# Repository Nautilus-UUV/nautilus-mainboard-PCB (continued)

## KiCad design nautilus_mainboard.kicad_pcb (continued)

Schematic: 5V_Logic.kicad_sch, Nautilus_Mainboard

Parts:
C35, C36: 10uF; C_1210_3225Metric; Voltage 100V; Tolerance 10%; MPN GRM32EC72A106KE05; LCSC C5444485
C37, C38, C40: 100nF; C_0603_1608Metric; Voltage 50V; Tolerance 10%; MPN 885012206095; LCSC CXXXXX
C41: 330nF; C_0603_1608Metric; Voltage 10V; Tolerance 20%; MPN 885012106007; LCSC CXXXXX
C53: 47uF; C_0805_2012Metric; Voltage 10V; Tolerance 20%; MPN GRM21BR61A476ME15; LCSC C124129
IC5: TPS2121RUXT; TI_Switchover_TPS2121RUXT; Mouser Part Number 595-TPS2121RUXT
R22: 22k; R_0603_1608Metric; Tolerance 1 %; MPN 560112116022; LCSC CXXXXX

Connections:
+5V: C40.1, C53.1, IC5.1 (OUT_1), IC5.8 (OUT_2); also elsewhere on the board
/Power_logic/5V_Logic/Battery_Out_5V: C35.1, C37.1, IC5.6 (PR1), IC5.7 (IN1); also elsewhere on the board
/Power_logic/5V_Logic/USB_Out_5V: C36.1, C38.1, IC5.2 (IN2); also elsewhere on the board
GND: C35.2, C36.2, C37.2, C38.2, C40.2, C41.1, C53.2, IC5.3 (CP2), IC5.4 (OV2), IC5.5 (OV1), IC5.12 (GND), R22.1; also elsewhere on the board
unnamed: IC5.10 (ILIM), R22.2
unnamed: C41.2, IC5.11 (SS)

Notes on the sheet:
for questions about wiring etc please consult the datasheet...
if the USB-only cold start "disconnects" we can try to bump SS to 470nF instead of 330nF.
100nF CLOSE
https://www.ti.com/lit/ds/symlink/tps2120.pdf?ts=1761678178328
PR1 > CP2 -> IN1 has prio

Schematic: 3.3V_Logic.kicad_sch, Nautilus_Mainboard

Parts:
C21, C22: 10uF; C_1210_3225Metric; Voltage 100V; Tolerance 10%; MPN GRM32EC72A106KE05; LCSC C5444485
C23, C24, C26: 100nF; C_0603_1608Metric; Voltage 50V; Tolerance 10%; MPN 885012206095; LCSC CXXXXX
C25: 330nF; C_0603_1608Metric; Voltage 10V; Tolerance 20%; MPN 885012106007; LCSC CXXXXX
C27: 47uF; C_0805_2012Metric; Voltage 10V; Tolerance 20%; MPN GRM21BR61A476ME15; LCSC C124129
IC6: TPS2121RUXT; TI_Switchover_TPS2121RUXT; Mouser Part Number 595-TPS2121RUXT
R17: 68k; R_0603_1608Metric; Tolerance 1 %; MPN 560112116064; LCSC CXXXXX

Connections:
+3.3V: C26.1, C27.1, IC6.1 (OUT_1), IC6.8 (OUT_2); also elsewhere on the board
/Power_logic/3.3V_Logic/Battery_Out_3.3V: C21.1, C23.1, IC6.6 (PR1), IC6.7 (IN1); also elsewhere on the board
/Power_logic/3.3V_Logic/STM_Plug_3.3V: C22.1, C24.1, IC6.2 (IN2); also elsewhere on the board
GND: C21.2, C22.2, C23.2, C24.2, C25.1, C26.2, C27.2, IC6.3 (CP2), IC6.4 (OV2), IC6.5 (OV1), IC6.12 (GND), R17.2; also elsewhere on the board
unnamed: IC6.10 (ILIM), R17.1
unnamed: C25.2, IC6.11 (SS)

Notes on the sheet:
if the USB-only cold start "disconnects" we can try to bump SS to 470nF instead of 330nF.
22 kΩ → ~4.55 A 39 kΩ → ~2.78 A 50 kΩ → ~2.25 A 56 kΩ → ~2.04 A 68 kΩ → ~1.72 A 100 kΩ → ~1.24 A
Pin 10: 68k leads to about 1.72A (should be enough for STM)
[R] = [kOhm] 65.2 / R^0.861
PR1 > CP2 -> IN1 has prio

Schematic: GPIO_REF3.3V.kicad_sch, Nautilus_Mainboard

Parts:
C39, C50, C51, C52: 100nF; C_0603_1608Metric; Voltage 50V; Tolerance 10%; MPN 885012206095; LCSC CXXXXX
C48, C49: 10uF; C_1210_3225Metric; Voltage 100V; Tolerance 10%; MPN GRM32EC72A106KE05; LCSC C5444485
C54: 47uF; C_0805_2012Metric; Voltage 10V; Tolerance 20%; MPN GRM21BR61A476ME15; LCSC C124129
IC3: TPS2121RUXT; TI_Switchover_TPS2121RUXT; Mouser Part Number 595-TPS2121RUXT
R14, R27: 100k; R_0603_1608Metric; Tolerance 1 %; MPN 560112116004; LCSC CXXXXX
TP13: Test Point; TestPoint_Pad_D1.5mm

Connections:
/CM4/GPIO_VREF_3.3V: C52.1, C54.1, IC3.1 (OUT_1), IC3.8 (OUT_2), R14.1, TP13.1; also elsewhere on the board
/Power_logic/GPIO_REF3.3V/CM4_OUT_3.3V: C49.1, C51.1, IC3.2 (IN2); also elsewhere on the board
/Power_logic/GPIO_REF3.3V/STM_IN_3.3V: C48.1, C50.1, IC3.6 (PR1), IC3.7 (IN1); also elsewhere on the board
GND: C39.1, C48.2, C49.2, C50.2, C51.2, C52.2, C54.2, IC3.3 (CP2), IC3.4 (OV2), IC3.5 (OV1), IC3.12 (GND), R14.2, R27.1; also elsewhere on the board
unnamed: IC3.10 (ILIM), R27.2
unnamed: C39.2, IC3.11 (SS)

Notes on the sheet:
Pin SS (11): 100nF soft start cap more than enoug as virtually no load at all at vref
PR1 > CP2 -> IN1 has prio
[R] = [kOhm] 65.2 / R^0.861
100kOhm pulldown so Vref is low if everything is off (not floating)
22 kΩ → ~4.55 A 39 kΩ → ~2.78 A 50 kΩ → ~2.25 A 56 kΩ → ~2.04 A 68 kΩ → ~1.72 A 100 kΩ → ~1.24 A
Pin 10: 100kOhm leads to about 1.24A (absolute overkill)

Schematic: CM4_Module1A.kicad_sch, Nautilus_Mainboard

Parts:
C1, C2, C3, C4, C5, C6: 100nF; C_0603_1608Metric; Voltage 50V; Tolerance 10%; MPN 885012206095; LCSC CXXXXX
C7, C42: 1uF; C_0603_1608Metric; Voltage 50V; Tolerance 10%; MPN 885012206126; LCSC CXXXXX
C47: 10uF; C_1210_3225Metric; Voltage 100V; Tolerance 10%; MPN GRM32EC72A106KE05; LCSC C5444485
Module1: DF40C-100DS-0.4V(51); Con-Raspberry-Pi-4-Compute-Module; Part Description 100 Position Connector Receptacle, Cent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; LCSC N/A
Q2: 50V; onsemi_Mosfet_BSS138; PARTREV 30 Jan 2018

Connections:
+5V: C1.1, C2.1, C3.1, C4.1, C5.1, C6.1, C7.1, C42.1, C47.1, Module1.77 (+5v_(Input)), Module1.79 (+5v_(Input)), Module1.81 (+5v_(Input)), Module1.83 (+5v_(Input)), Module1.85 (+5v_(Input)), Module1.87 (+5v_(Input)); also elsewhere on the board
/CM4/CM4_Module1A/CM4_LED1/nPWR_LED: Module1.95 (nPI_LED_PWR); also elsewhere on the board
/CM4/CM4_Module1A/CM4_LED2/PI_nLED_Activity: Module1.21 (PI_nLED_Activity); also elsewhere on the board
/CM4/CM4_Module1A/ETH_LED_G: Module1.15 (Ethernet_nLED3(3.3v)); also elsewhere on the board
/CM4/CM4_Module1A/ETH_LED_Y: Module1.17 (Ethernet_nLED2(3.3v)); also elsewhere on the board
/CM4/CM4_Module1A/GLOBAL_EN: Module1.99 (Global_EN), Q2.3
/CM4/CM4_Module1A/GPIO2: Module1.58 (GPIO2)
/CM4/CM4_Module1A/GPIO3: Module1.56 (GPIO3)
/CM4/CM4_Module1A/GPIO4: Module1.54 (GPIO4)
/CM4/CM4_Module1A/GPIO5: Module1.34 (GPIO5)
/CM4/CM4_Module1A/GPIO6: Module1.30 (GPIO6)
/CM4/CM4_Module1A/GPIO7: Module1.37 (GPIO7)
/CM4/CM4_Module1A/GPIO8: Module1.39 (GPIO8)
/CM4/CM4_Module1A/GPIO9: Module1.40 (GPIO9)
/CM4/CM4_Module1A/GPIO10: Module1.44 (GPIO10)
/CM4/CM4_Module1A/GPIO11: Module1.38 (GPIO11)
/CM4/CM4_Module1A/GPIO12: Module1.31 (GPIO12)
/CM4/CM4_Module1A/GPIO13: Module1.28 (GPIO13)
/CM4/CM4_Module1A/GPIO16: Module1.29 (GPIO16)
/CM4/CM4_Module1A/GPIO17: Module1.50 (GPIO17)
/CM4/CM4_Module1A/GPIO18: Module1.49 (GPIO18)
/CM4/CM4_Module1A/GPIO19: Module1.26 (GPIO19)
/CM4/CM4_Module1A/GPIO20: Module1.27 (GPIO20)
/CM4/CM4_Module1A/GPIO21: Module1.25 (GPIO21)
/CM4/CM4_Module1A/GPIO22: Module1.46 (GPIO22)
/CM4/CM4_Module1A/GPIO23: Module1.47 (GPIO23)
/CM4/CM4_Module1A/GPIO24: Module1.45 (GPIO24)
/CM4/CM4_Module1A/GPIO25: Module1.41 (GPIO25)
/CM4/CM4_Module1A/GPIO26: Module1.24 (GPIO26)
/CM4/CM4_Module1A/GPIO27: Module1.48 (GPIO27)
/CM4/CM4_Out_3.3V: Module1.84 (+3.3v_(Output)), Module1.86 (+3.3v_(Output)); also elsewhere on the board
/CM4/GLOBAL_EN_CM4: Q2.1; also elsewhere on the board
/CM4/GPIO_VREF_3.3V: Module1.78 (GPIO_VREF(1.8v/3.3v_Input)); also elsewhere on the board
/CM4/RUN_PG: Module1.92 (RUN_PG); also elsewhere on the board
/CM4/TRD0.D+: Module1.12 (Ethernet_Pair0_P); also elsewhere on the board
/CM4/TRD0.D-: Module1.10 (Ethernet_Pair0_N); also elsewhere on the board
/CM4/TRD1.D+: Module1.4 (Ethernet_Pair1_P); also elsewhere on the board
/CM4/TRD1.D-: Module1.6 (Ethernet_Pair1_N); also elsewhere on the board
/CM4/TRD2.D+: Module1.11 (Ethernet_Pair2_P); also elsewhere on the board
/CM4/TRD2.D-: Module1.9 (Ethernet_Pair2_N); also elsewhere on the board
/CM4/TRD3.D+: Module1.3 (Ethernet_Pair3_P); also elsewhere on the board
/CM4/TRD3.D-: Module1.5 (Ethernet_Pair3_N); also elsewhere on the board
/STM/PinoutSTM/USART2_RX: Module1.55 (GPIO14); also elsewhere on the board
/STM/PinoutSTM/USART2_TX: Module1.51 (GPIO15); also elsewhere on the board
GND: C1.2, C2.2, C3.2, C4.2, C5.2, C6.2, C7.2, C42.2, C47.2, Module1.1 (GND), Module1.2 (GND), Module1.7 (GND), Module1.8 (GND), Module1.13 (GND), Module1.14 (GND), Module1.22 (GND), Module1.23 (GND), Module1.32 (GND), Module1.33 (GND), Module1.42 (GND), Module1.43 (GND), Module1.52 (GND), Module1.53 (GND), Module1.59 (GND), Module1.60 (GND), Module1.65 (GND), Module1.66 (GND), Module1.71 (GND), Module1.74 (GND), Module1.89 (WL_nDisable), Module1.91 (BT_nDisable), Module1.98 (GND), Q2.2; also elsewhere on the board

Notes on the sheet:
N/A
connect Wlan to gnd if off, and leave floating for on. Please use a 2 pin connector here with a jumper cap. (has to be done)
GLOBAL_EN needs to be pulled low for >1ms after software shutdown.
Disable Wlan and Bluetooth?
Ethernet connection
GLOBAL_EN logic
Decoupling for CM4 5V inputs

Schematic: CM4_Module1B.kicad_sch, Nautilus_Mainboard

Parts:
C20: 4.7nF; C_0603_1608Metric; Voltage 50V; Tolerance 10%; MPN 885012206087; LCSC CXXXXX
D5: 595-TPD2EUSB30DRTR; TI_Prot_TPD2EUSB30DRTR; Mouser Part Number 595-TPD2EUSB30DRTR
D6: SMF5.0A-TP; SMF50ATP; MPN 833-SMF5.0A-TP
J3: 179-UJ20CHC4SMTTR; CON_Samesky_CUI_UJ20-C-H-C-4-SMT-TR; PARTREV 1.0
LED3: 710-150060RS83000; Wuerth_LED_150060RS83000; Manufacturer_Part_Number 150060RS83000
Module1: DF40C-100DS-0.4V(51); Con-Raspberry-Pi-4-Compute-Module; Part Description 100 Position Connector Receptacle, Cent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; LCSC N/A
R9: 1k; R_0603_1608Metric; Tolerance 1 %; MPN 560112116014; LCSC CXXXXX
R10, R12: 4.99k; R_0603_1608Metric; Tolerance 1 %; MPN 560112116132; LCSC CXXXXX
R11: 1M; R_0603_1608Metric; Tolerance 1 %; MPN 560112116074; LCSC CXXXXX

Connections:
/CM4/CM4_Module1B/PCIE_CLK._N: Module1.112 (PCIe_CLK_N); also elsewhere on the board
/CM4/CM4_Module1B/PCIE_CLK._P: Module1.110 (PCIe_CLK_P); also elsewhere on the board
/CM4/CM4_Module1B/PCIE_RX._N: Module1.118 (PCIe_RX_N); also elsewhere on the board
/CM4/CM4_Module1B/PCIE_RX._P: Module1.116 (PCIe_RX_P); also elsewhere on the board
/CM4/CM4_Module1B/PCIE_TX._N: Module1.124 (PCIe_TX_N); also elsewhere on the board
/CM4/CM4_Module1B/PCIE_TX._P: Module1.122 (PCIe_TX_P); also elsewhere on the board
/CM4/CM4_Module1B/PCIE_nRST: Module1.109 (PCIe_nRST); also elsewhere on the board
/CM4/CM4_Module1B/USB_D+: D5.2 (D-), J3.A6 (DP1), J3.B6 (DP2), Module1.105 (USB2_P)
/CM4/CM4_Module1B/USB_D-: D5.1 (D+), J3.A7 (DN1), J3.B7 (DN2), Module1.103 (USB2_N)
/CM4/CM4_Module1B/USB_OTG_ID: Module1.101 (USB_OTG_ID); also elsewhere on the board
/CM4/USB_Out_5V: D6.1 (K), J3.A4_B9 (VBUS), J3.A9_B4 (VBUS), LED3.2 (A); also elsewhere on the board
GND: C20.1, D5.3 (GND), D6.2 (A), J3.A1_B12 (GND), J3.A12_B1 (GND), Module1.107 (GND), Module1.108 (GND), Module1.113 (GND), Module1.114 (GND), Module1.119 (GND), Module1.120 (GND), Module1.125 (GND), Module1.126 (GND), Module1.131 (GND), Module1.132 (GND), Module1.137 (GND), Module1.138 (GND), Module1.144 (GND), Module1.150 (GND), Module1.155 (GND), Module1.156 (GND), Module1.161 (GND), Module1.162 (GND), Module1.167 (GND), Module1.168 (GND), Module1.173 (GND), Module1.174 (GND), Module1.179 (GND), Module1.180 (GND), Module1.185 (GND), Module1.186 (GND), Module1.191 (GND), Module1.192 (GND), Module1.197 (GND), Module1.198 (GND), R9.2, R10.2, R11.2, R12.2; also elsewhere on the board
unnamed: C20.2, J3.SH1 (SHIELD), J3.SH2 (SHIELD), J3.SH3 (SHIELD), J3.SH4 (SHIELD), R11.1
unnamed: J3.A5 (CC1), R10.1
unnamed: J3.B5 (CC2), R12.1
unnamed: LED3.1 (K), R9.1

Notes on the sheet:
old usb port for reference.
Can be kept floating. if no usb is connected
maybe RX and TX need to be switched
WIP, nRPI_BOOT? power only to certain parts? -> Diode (later) indication? (YES! LED)
Super important to not differ lengths or curve a lot with D+ and D-. Also should have same hole counts (vias) and same length.
ESD protection for the USB
USB Connection for CM4

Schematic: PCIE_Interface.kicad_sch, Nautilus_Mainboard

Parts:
J6: MDT275M02001; PCIE_MDT275M02001; Mouser Part Number 523-MDT275M02001
JP14, JP15, JP16, JP17: -; SolderJumper-2_P1.3mm_Open_RoundedPad1.0x1.5mm
LED4: 710-150060VS83000; Wuerth_LED_150060RS83000; Manufacturer_Part_Number 150060RS83000
R13: 1k; R_0603_1608Metric; Tolerance 1 %; MPN 560112116014; LCSC CXXXXX

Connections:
/CM4/Battery_Out_3.3V: J6.2, J6.4, J6.12, J6.14, J6.16, J6.18, J6.70, J6.72, J6.74, R13.2; also elsewhere on the board
/CM4/CM4_Module1B/PCIE_CLK._N: J6.53; also elsewhere on the board
/CM4/CM4_Module1B/PCIE_CLK._P: J6.55; also elsewhere on the board
/CM4/CM4_Module1B/PCIE_RX._N: J6.41; also elsewhere on the board
/CM4/CM4_Module1B/PCIE_RX._P: J6.43; also elsewhere on the board
/CM4/CM4_Module1B/PCIE_TX._N: J6.47; also elsewhere on the board
/CM4/CM4_Module1B/PCIE_TX._P: J6.49; also elsewhere on the board
/CM4/CM4_Module1B/PCIE_nRST: J6.50; also elsewhere on the board
/CM4/PCIE_Interface/CLKREQ#: J6.52
/CM4/PCIE_Interface/CONFIG_0: J6.21, JP14.2 (B)
/CM4/PCIE_Interface/CONFIG_1: J6.69, JP15.2 (B)
/CM4/PCIE_Interface/CONFIG_2: J6.75, JP16.2 (B)
/CM4/PCIE_Interface/CONFIG_3: J6.1, JP17.2 (B)
/CM4/PCIE_Interface/LED1_M2: J6.10, LED4.2 (A), R13.1
/CM4/PCIE_Interface/NFG1: J6.56
/CM4/PCIE_Interface/NFG2: J6.58
/CM4/PCIE_Interface/PERn1: J6.29
/CM4/PCIE_Interface/PERn2: J6.17
/CM4/PCIE_Interface/PERn3: J6.5
/CM4/PCIE_Interface/PERp1: J6.31
/CM4/PCIE_Interface/PERp2: J6.19
/CM4/PCIE_Interface/PERp3: J6.7
/CM4/PCIE_Interface/PETn1: J6.35
/CM4/PCIE_Interface/PETn2: J6.23
/CM4/PCIE_Interface/PETn3: J6.11
/CM4/PCIE_Interface/PETp1: J6.37
/CM4/PCIE_Interface/PETp2: J6.25
/CM4/PCIE_Interface/PETp3: J6.13
/CM4/PCIE_Interface/PEWAKE#: J6.54
/CM4/PCIE_Interface/SUSCLK: J6.68
GND: J6.3, J6.9, J6.15, J6.27, J6.33, J6.39, J6.45, J6.51, J6.57, J6.71, J6.73, J6.76 (MP_1), J6.77 (MP_2), JP14.1 (A), JP15.1 (A), JP16.1 (A), JP17.1 (A), LED4.1 (K); also elsewhere on the board

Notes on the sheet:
Led indicator
Configuration 0-Ohm resistors

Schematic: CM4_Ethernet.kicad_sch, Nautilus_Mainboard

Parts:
LED5: 710-150060VS83000; Wuerth_LED_150060RS83000; Manufacturer_Part_Number 150060RS83000
LED6: 710-150060YS83000; Wuerth_LED_150060RS83000; Manufacturer_Part_Number 150060RS83000
R7, R8: 1k; R_0603_1608Metric; Tolerance 1 %; MPN 560112116014; LCSC CXXXXX
TPD4EUSB30DQAR1, TPD4EUSB30DQAR2: IC_TPD4EUSB30DQAR; PARTREV F; LCSC C90627

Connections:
/CM4/Battery_Out_3.3V: LED5.2 (A), LED6.2 (A); also elsewhere on the board
/CM4/CM4_Module1A/ETH_LED_G: R7.1; also elsewhere on the board
/CM4/CM4_Module1A/ETH_LED_Y: R8.1; also elsewhere on the board
/CM4/TRD0.D+: TPD4EUSB30DQAR2.1, TPD4EUSB30DQAR2.10 (Through_1); also elsewhere on the board
/CM4/TRD0.D-: TPD4EUSB30DQAR2.2, TPD4EUSB30DQAR2.9 (Through_2); also elsewhere on the board
/CM4/TRD1.D+: TPD4EUSB30DQAR2.5, TPD4EUSB30DQAR2.6 (Through_5); also elsewhere on the board
/CM4/TRD1.D-: TPD4EUSB30DQAR2.4, TPD4EUSB30DQAR2.7 (Through_4); also elsewhere on the board
/CM4/TRD2.D+: TPD4EUSB30DQAR1.1, TPD4EUSB30DQAR1.10 (Through_1); also elsewhere on the board
/CM4/TRD2.D-: TPD4EUSB30DQAR1.2, TPD4EUSB30DQAR1.9 (Through_2); also elsewhere on the board
/CM4/TRD3.D+: TPD4EUSB30DQAR1.5, TPD4EUSB30DQAR1.6 (Through_5); also elsewhere on the board
/CM4/TRD3.D-: TPD4EUSB30DQAR1.4, TPD4EUSB30DQAR1.7 (Through_4); also elsewhere on the board
GND: TPD4EUSB30DQAR1.3, TPD4EUSB30DQAR1.8, TPD4EUSB30DQAR2.3, TPD4EUSB30DQAR2.8; also elsewhere on the board
unnamed: LED5.1 (K), R7.2
unnamed: LED6.1 (K), R8.2

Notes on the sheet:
POE Protection

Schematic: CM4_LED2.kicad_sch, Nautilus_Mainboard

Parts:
LED7: 710-150060YS83000; Wuerth_LED_150060RS83000; Manufacturer_Part_Number 150060RS83000
R6: 1k; R_0603_1608Metric; Tolerance 1 %; MPN 560112116014; LCSC CXXXXX

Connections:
/CM4/Battery_Out_3.3V: LED7.2 (A); also elsewhere on the board
/CM4/CM4_Module1A/CM4_LED2/PI_nLED_Activity: R6.1; also elsewhere on the board
unnamed: LED7.1 (K), R6.2

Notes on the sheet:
Simple Activity LED
Activity LED

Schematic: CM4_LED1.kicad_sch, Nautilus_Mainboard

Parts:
LED8: 710-150060YS83000; Wuerth_LED_150060RS83000; Manufacturer_Part_Number 150060RS83000
R5: 1k; R_0603_1608Metric; Tolerance 1 %; MPN 560112116014; LCSC CXXXXX
U3: Buffers & Line Driver; SOT65P210X110-5N; MPN 74LVC1G07SE-7; LCSC C67531

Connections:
/CM4/Battery_Out_3.3V: LED8.2 (A), U3.5 (VCC); also elsewhere on the board
/CM4/CM4_Module1A/CM4_LED1/nPWR_LED: U3.2; also elsewhere on the board
GND: U3.3 (GND); also elsewhere on the board
unnamed: LED8.1 (K), R5.2
unnamed: R5.1, U3.4

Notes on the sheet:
From the CM4 io board
Directly copied from the official CM4 io board (indicator LED for 3.3v)
Screenshot

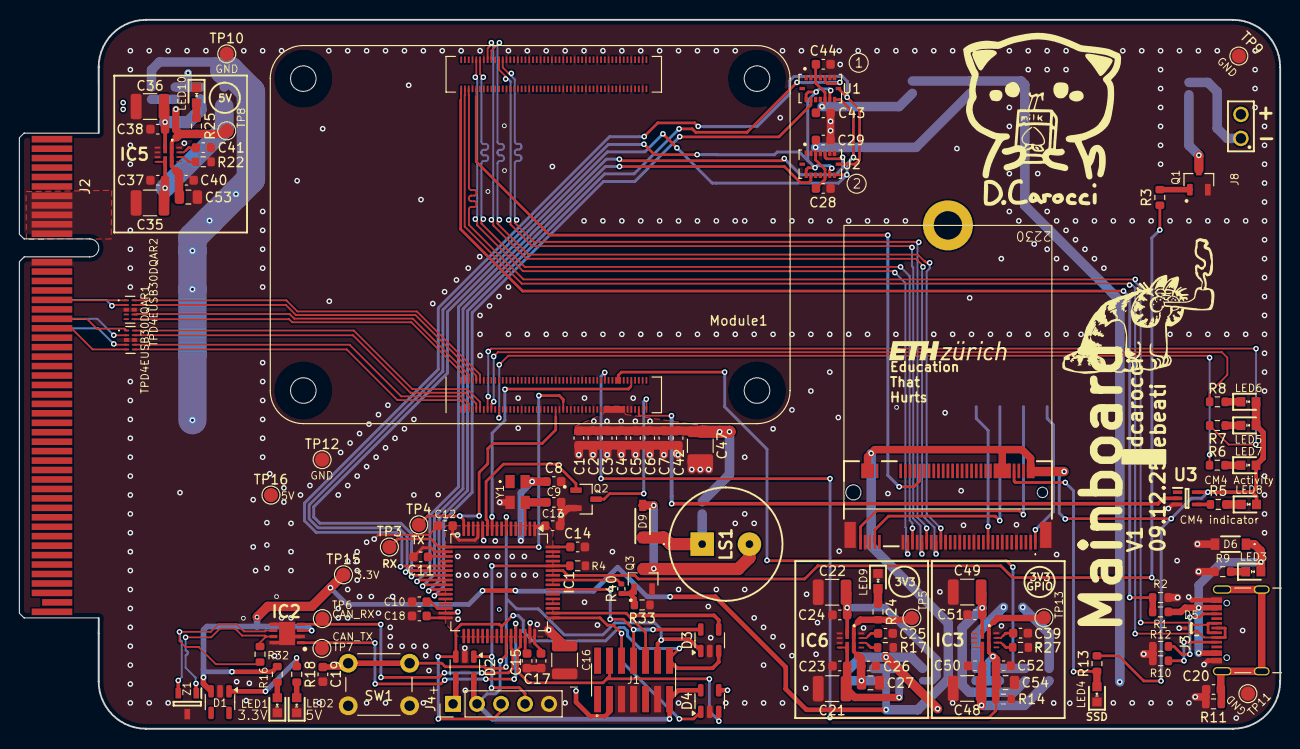
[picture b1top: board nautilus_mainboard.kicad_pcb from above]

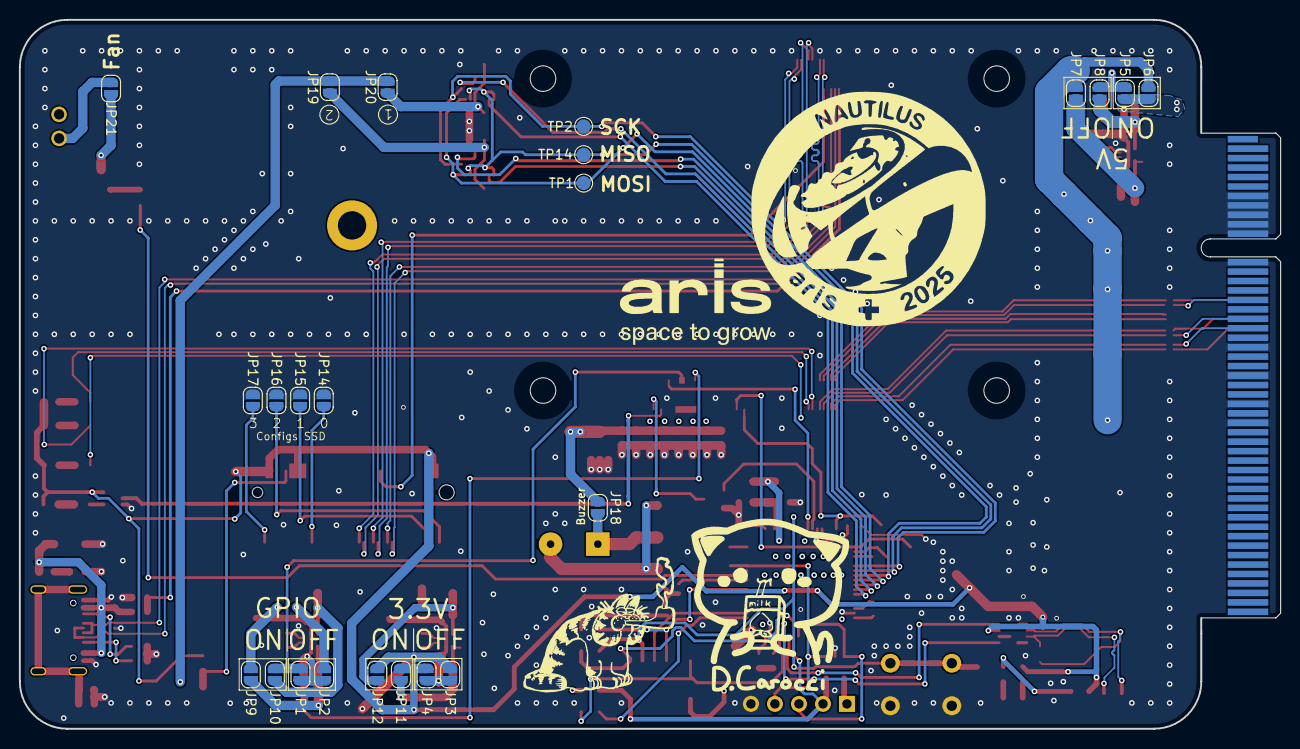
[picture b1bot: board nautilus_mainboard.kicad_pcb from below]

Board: 4 copper layers, 133.3 x 75.0 mm, 148 parts (23 on the bottom side), 101 nets.

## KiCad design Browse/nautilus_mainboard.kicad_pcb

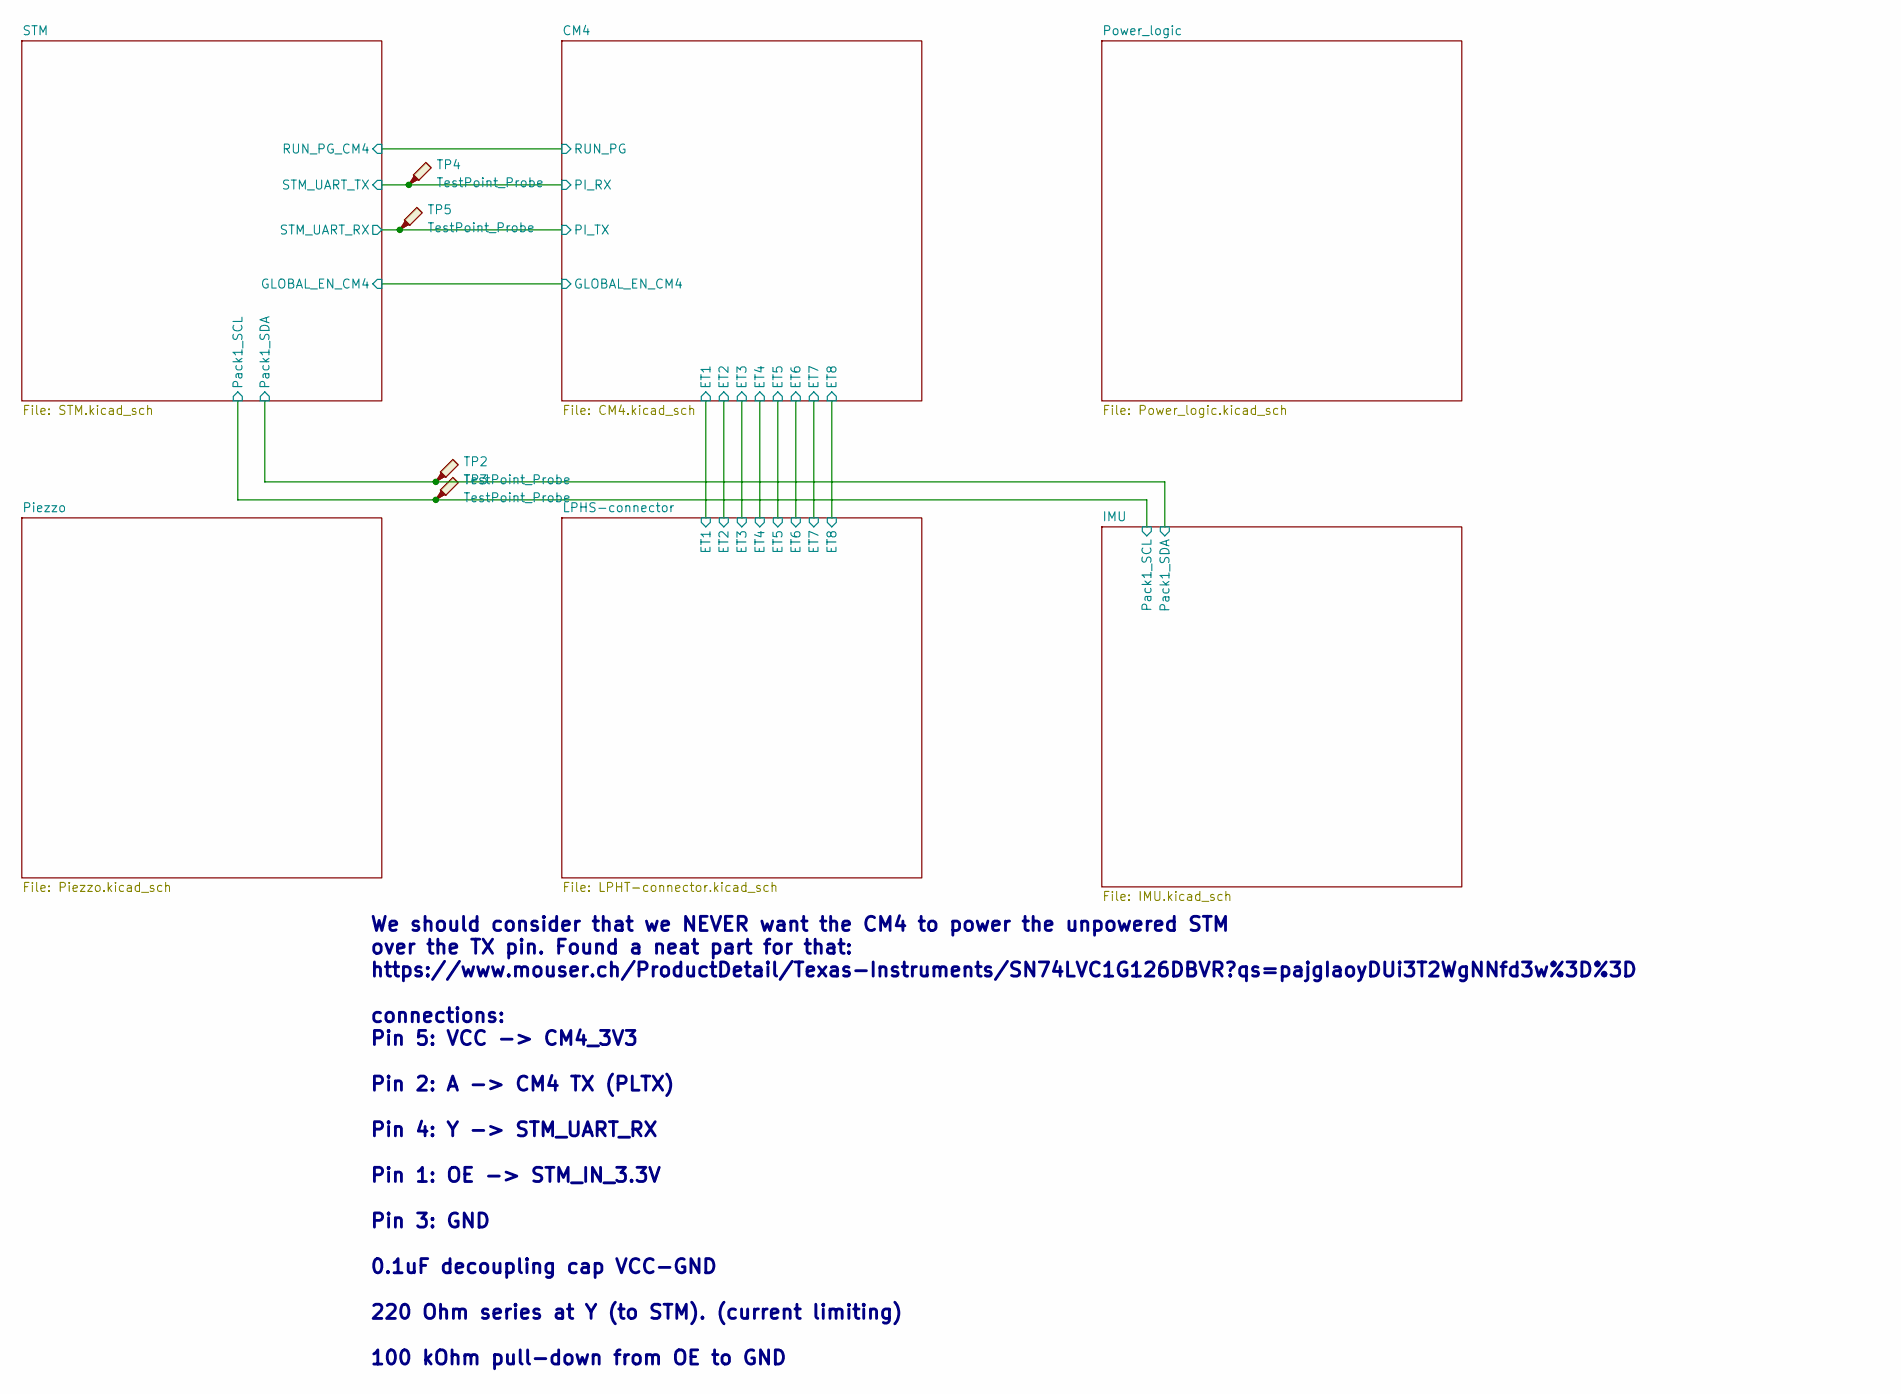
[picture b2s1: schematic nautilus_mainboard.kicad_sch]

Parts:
TP2, TP3: TestPoint_Probe; TestPoint_THTPad_D2.5mm_Drill1.2mm
TP4, TP5: TestPoint_Probe; TestPoint_Pad_D1.0mm

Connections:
/CM4/CM4_Module1A/GPIO14: TP5.1; also elsewhere on the board
/CM4/CM4_Module1A/GPIO15: TP4.1; also elsewhere on the board
/IMU/Pack1_SCL: TP3.1; also elsewhere on the board
/IMU/Pack1_SDA: TP2.1; also elsewhere on the board

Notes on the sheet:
We should consider that we NEVER want the CM4 to power the unpowered STM over the TX pin. Found a neat part for that: https://www.mouser.ch/ProductDetail/Texas-Instruments/SN74LVC1G126DBVR?qs=pajgIaoyDUi3T2WgNNfd3w%3D%3D connections: Pin 5: VCC -> CM4_3V3 Pin 2: A -> CM4 TX (PLTX) Pin 4: Y -> STM_U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

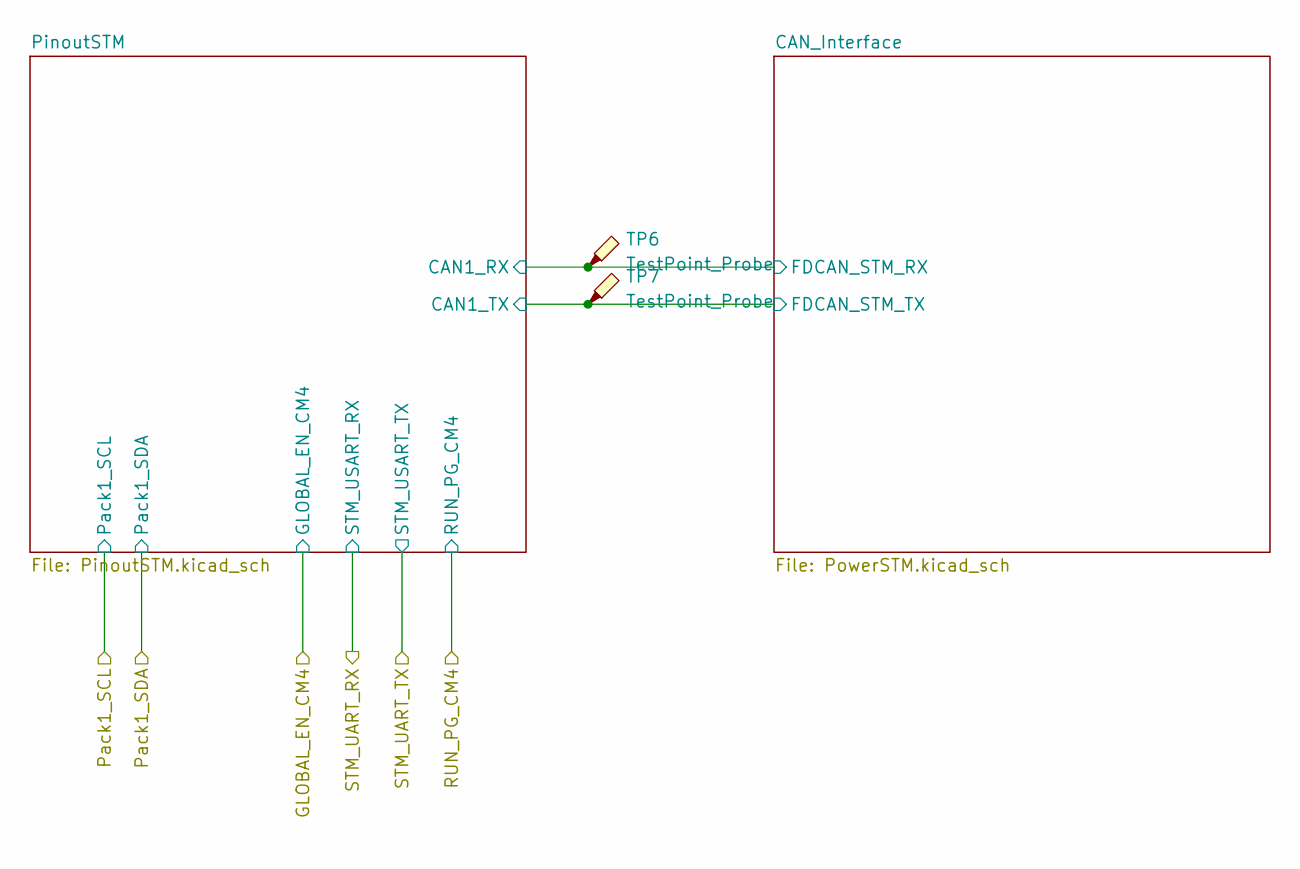
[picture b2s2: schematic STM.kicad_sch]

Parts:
TP6, TP7: TestPoint_Probe; TestPoint_THTPad_D2.5mm_Drill1.2mm

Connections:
/STM/PinoutSTM/CAN1_RX: TP6.1; also elsewhere on the board
/STM/PinoutSTM/CAN1_TX: TP7.1; also elsewhere on the board

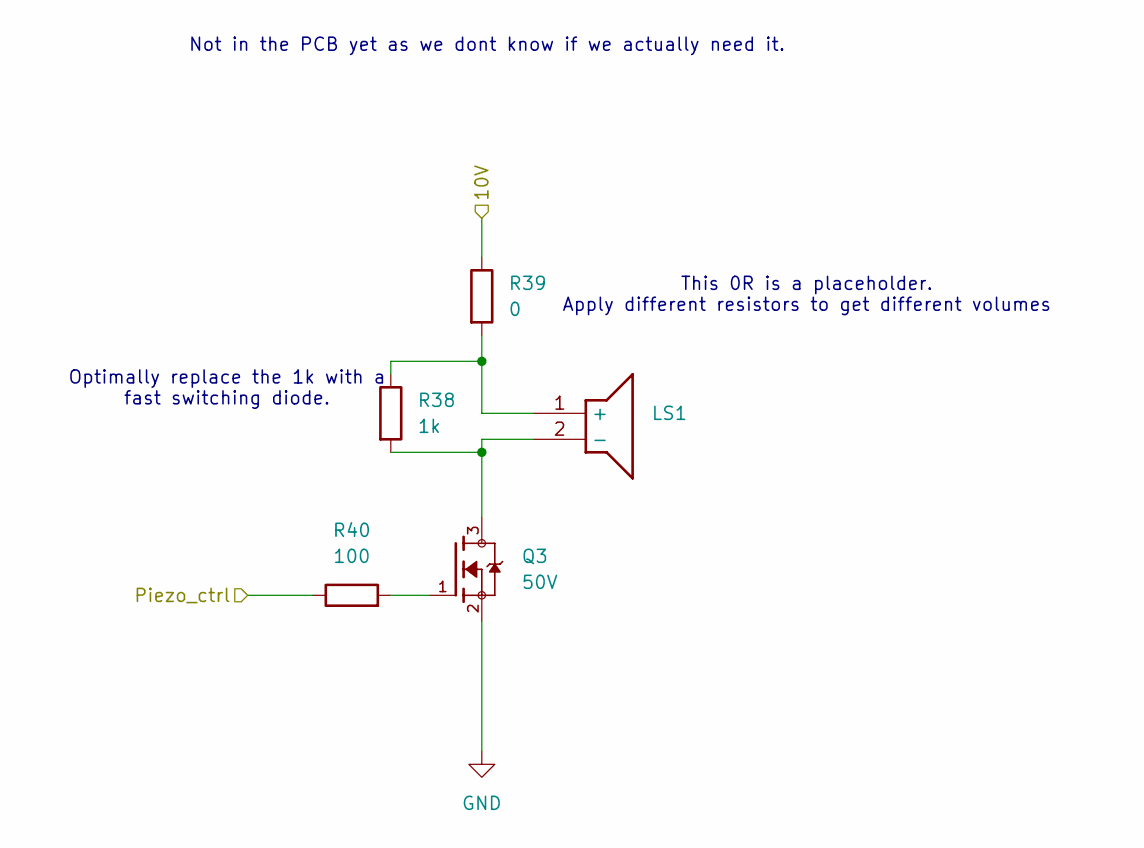
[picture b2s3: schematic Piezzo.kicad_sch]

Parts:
LS1: PT-1140PEQ; Mouser Part Number 539-PT-1140PEQ
Q3: 50V; onsemi_Mosfet_BSS138; PARTREV 30 Jan 2018
R38: 1k; R_0603_1608Metric; Tolerance 1 %; MPN 560112116014; LCSC CXXXXX
R39: 0; R_0603_1608Metric; Tolerance 5%; MPN 560112116001; LCSC CXXXXX
R40: 100; R_0402_1005Metric; Tolerance 1%; MPN ERJ-2RKF1000X; LCSC C413063

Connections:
unnamed: LS1.1 (+), R38.1, R39.2
unnamed: LS1.2 (-), Q3.3, R38.2
unnamed: Q3.1, R40.2

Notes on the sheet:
Optimally replace the 1k with a fast switching diode.
This 0R is a placeholder. Apply different resistors to get different volumes
Not in the PCB yet as we dont know if we actually need it.

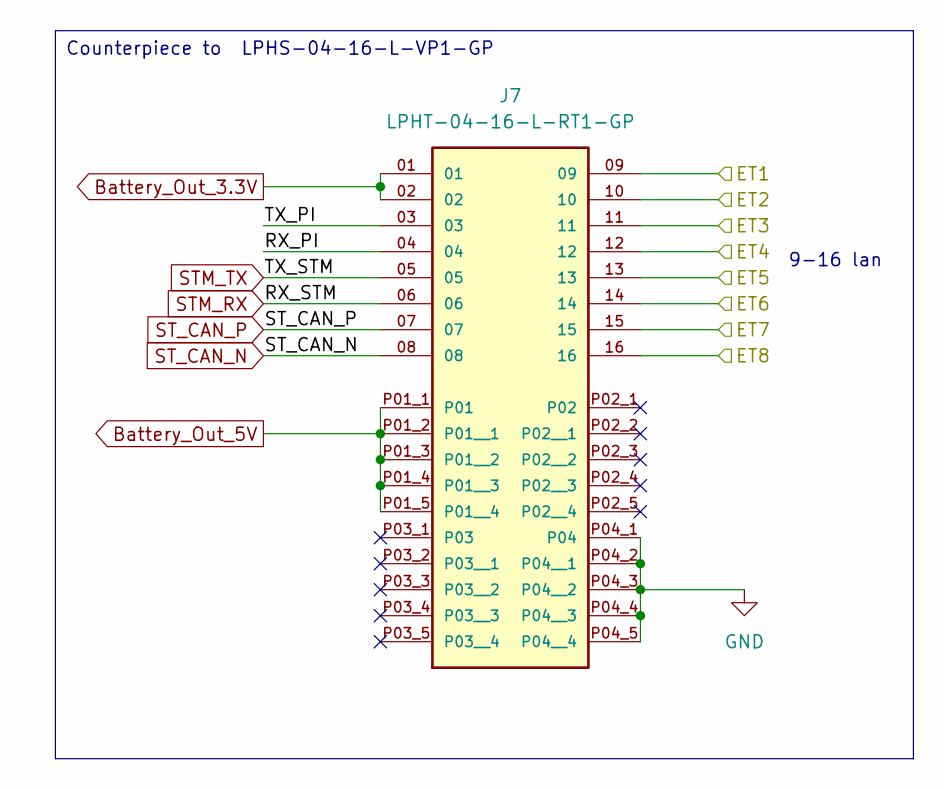
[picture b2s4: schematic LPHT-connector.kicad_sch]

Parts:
J7: LPHT-04-16-L-RT1-GP; SAMTEC_LPHT-04-16-X-RT1-GP; PARTREV C; LCSC CXXXXX

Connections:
/CM4/CM4_Module1A/TRD0_N: J7.09; also elsewhere on the board
/CM4/CM4_Module1A/TRD0_P: J7.10; also elsewhere on the board
/CM4/CM4_Module1A/TRD1_N: J7.11; also elsewhere on the board
/CM4/CM4_Module1A/TRD1_P: J7.12; also elsewhere on the board
/CM4/CM4_Module1A/TRD2_N: J7.13; also elsewhere on the board
/CM4/CM4_Module1A/TRD2_P: J7.14; also elsewhere on the board
/CM4/CM4_Module1A/TRD3_N: J7.15; also elsewhere on the board
/CM4/CM4_Module1A/TRD3_P: J7.16; also elsewhere on the board
/LPHS-connector/RX_PI: J7.04
/LPHS-connector/TX_PI: J7.03
Battery_Out_5V: J7.P01_1 (P01), J7.P01_2 (P01__1), J7.P01_3 (P01__2), J7.P01_4 (P01__3), J7.P01_5 (P01__4); also elsewhere on the board
GND: J7.P04_1 (P04), J7.P04_2 (P04__1), J7.P04_3 (P04__2), J7.P04_4 (P04__3), J7.P04_5 (P04__4); also elsewhere on the board
STM_RX: J7.06; also elsewhere on the board
STM_TX: J7.05; also elsewhere on the board
ST_CAN_N: J7.08; also elsewhere on the board
ST_CAN_P: J7.07; also elsewhere on the board

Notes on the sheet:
Counterpiece to LPHS-04-16-L-VP1-GP
9-16 lan

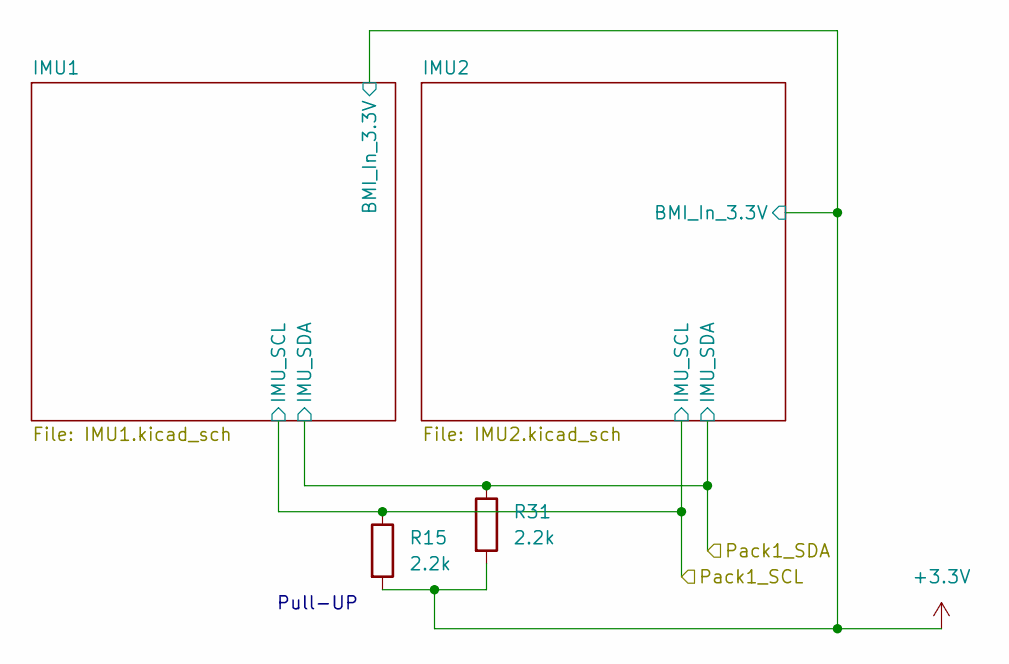
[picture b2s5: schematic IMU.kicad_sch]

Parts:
R15, R31: 2.2k; R_0603_1608Metric; Tolerance 1 %; MPN 560112116098; LCSC CXXXXX

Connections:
/IMU/Pack1_SCL: R15.1; also elsewhere on the board
/IMU/Pack1_SDA: R31.1; also elsewhere on the board
BMI_IN_3.3V: R15.2, R31.2; also elsewhere on the board

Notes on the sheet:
Pull-UP

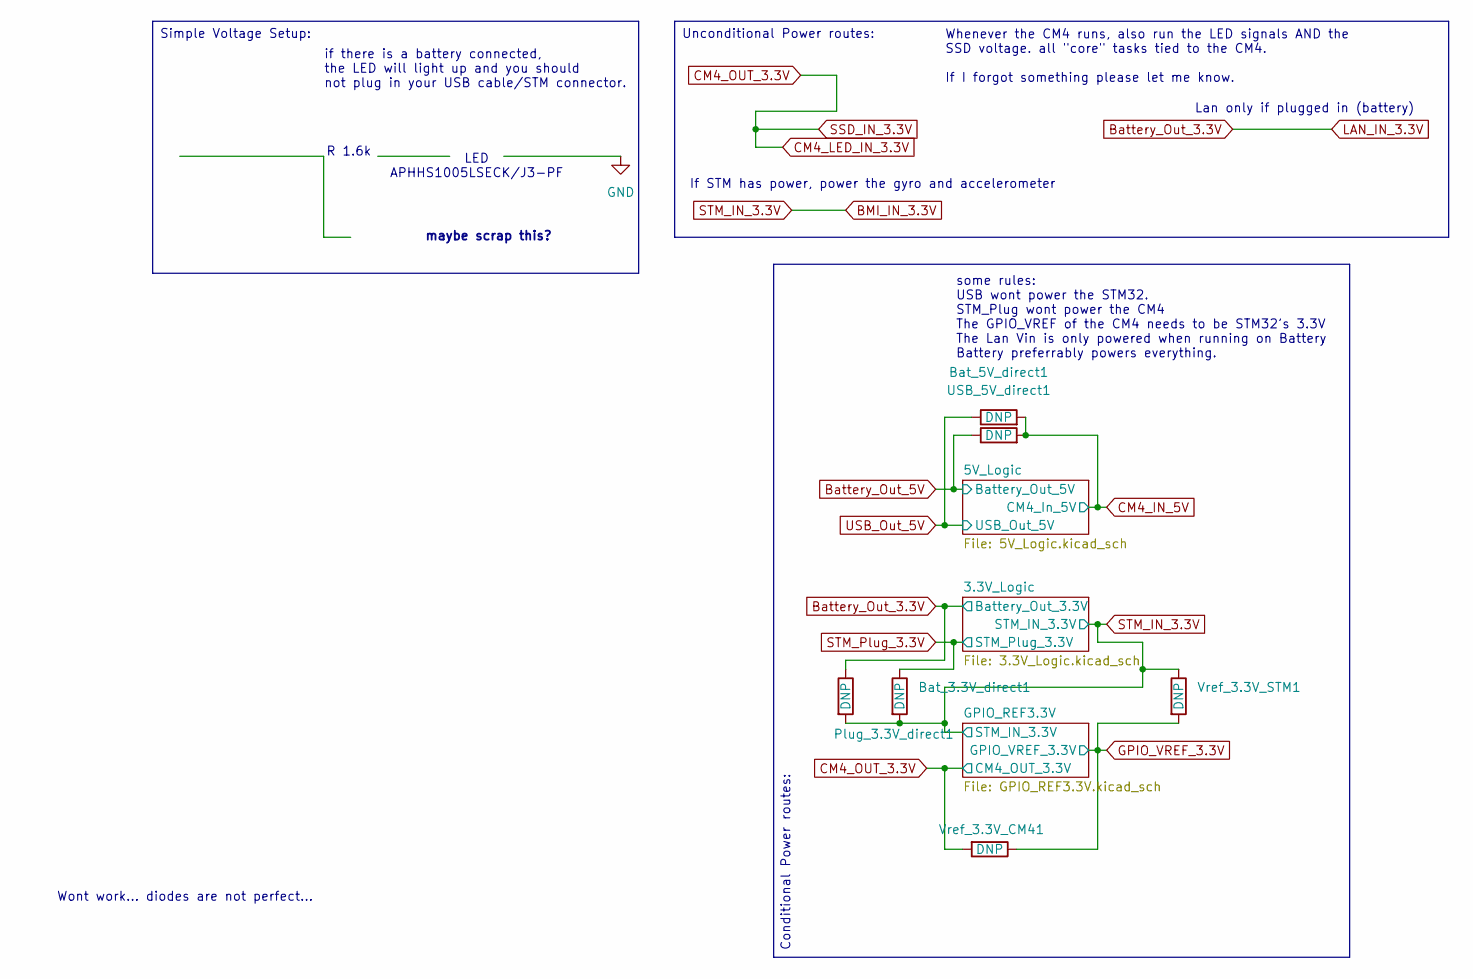
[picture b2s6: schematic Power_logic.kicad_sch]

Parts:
Bat_3.3V_direct1, Bat_5V_direct1: DNP; R_0603_1608Metric; Tolerance 5%; MPN 560112116001; LCSC CXXXXX
Plug_3.3V_direct1: DNP; R_0603_1608Metric; Tolerance 5%; MPN 560112116001; LCSC CXXXXX
USB_5V_direct1: DNP; R_0603_1608Metric; Tolerance 5%; MPN 560112116001; LCSC CXXXXX
Vref_3.3V_CM41, Vref_3.3V_STM1: DNP; R_0603_1608Metric; Tolerance 5%; MPN 560112116001; LCSC CXXXXX

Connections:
BMI_IN_3.3V: Bat_3.3V_direct1.2, Plug_3.3V_direct1.2, Vref_3.3V_STM1.1; also elsewhere on the board
Battery_Out_5V: USB_5V_direct1.1; also elsewhere on the board
CM4_IN_5V: Bat_5V_direct1.2, USB_5V_direct1.2; also elsewhere on the board
GPIO_VREF_3.3V: Vref_3.3V_CM41.1, Vref_3.3V_STM1.2; also elsewhere on the board
STM_Plug_3.3V: Bat_3.3V_direct1.1; also elsewhere on the board
USB_Out_5V: Bat_5V_direct1.1; also elsewhere on the board

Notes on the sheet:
Conditional Power routes:
Simple Voltage Setup:
Unconditional Power routes:
Wont work... diodes are not perfect...
if there is a battery connected, the LED will light up and you should not plug in your USB cable/STM connector.
If STM has power, power the gyro and accelerometer
maybe scrap this?
Whenever the CM4 runs, also run the LED signals AND the SSD voltage. all "core" tasks tied to the CM4. If I forgot something please let me know.
R 1.6k
Lan only if plugged in (battery)
LED APHHS1005LSECK/J3-PF
some rules: USB wont power the STM32. STM_Plug wont power the CM4 The GPIO_VREF of the CM4 needs to be STM32's 3.3V The Lan Vin is only powered when running on Battery Battery preferrably powers everything.
